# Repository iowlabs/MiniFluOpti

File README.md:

# MiniFluOpti

Versión mini del proyecto FluOpti. Desarrollo conjunto con equipo docente del Instituto de Ingeniería Biológica UC. 
Este proyecto consiste en un controlador de LEDs configurable por I2C. La placa controla 4 canales controladores de LEDs, por medio de señales PWM generadas *on-board*. Los grupos de LEDs considerado para esta versión son: rojos, verde, azul y blanco. Adicionalmente la placa 
incluye un controlador de *heater* y un par de canales de lectura de sensores de temperatura del tipo termistor.

## Características:

* Voltaje de entrada 12[V].
* 4 Canales de salida LEDs: Rojo, Verde, Azul, Blanco.
* 1 Controlador de heater. Max: 12[V] - 3[A]
* 2 Canales de lector de termistor.
* Voltaje de salida para alimentar Rpi 5[V] 2.5[A] (Raspy 3b+)
* Voltaje en placa 3.3[V] para componentes digitales.
* Voltajes disponibles: 3.3[V] 5[V], 9[V] y 12[V]
* Protocolo de control: I2C (deseado)
 
Dependencias:
* Generador de PWMs PCA9685
* Drivers de corriente IRF740
* Drivers de baja corriente (500mA) ULN2803A
* Lector de termistor MAX6682
* Reguladores de voltaje
* Conversores DC-DC

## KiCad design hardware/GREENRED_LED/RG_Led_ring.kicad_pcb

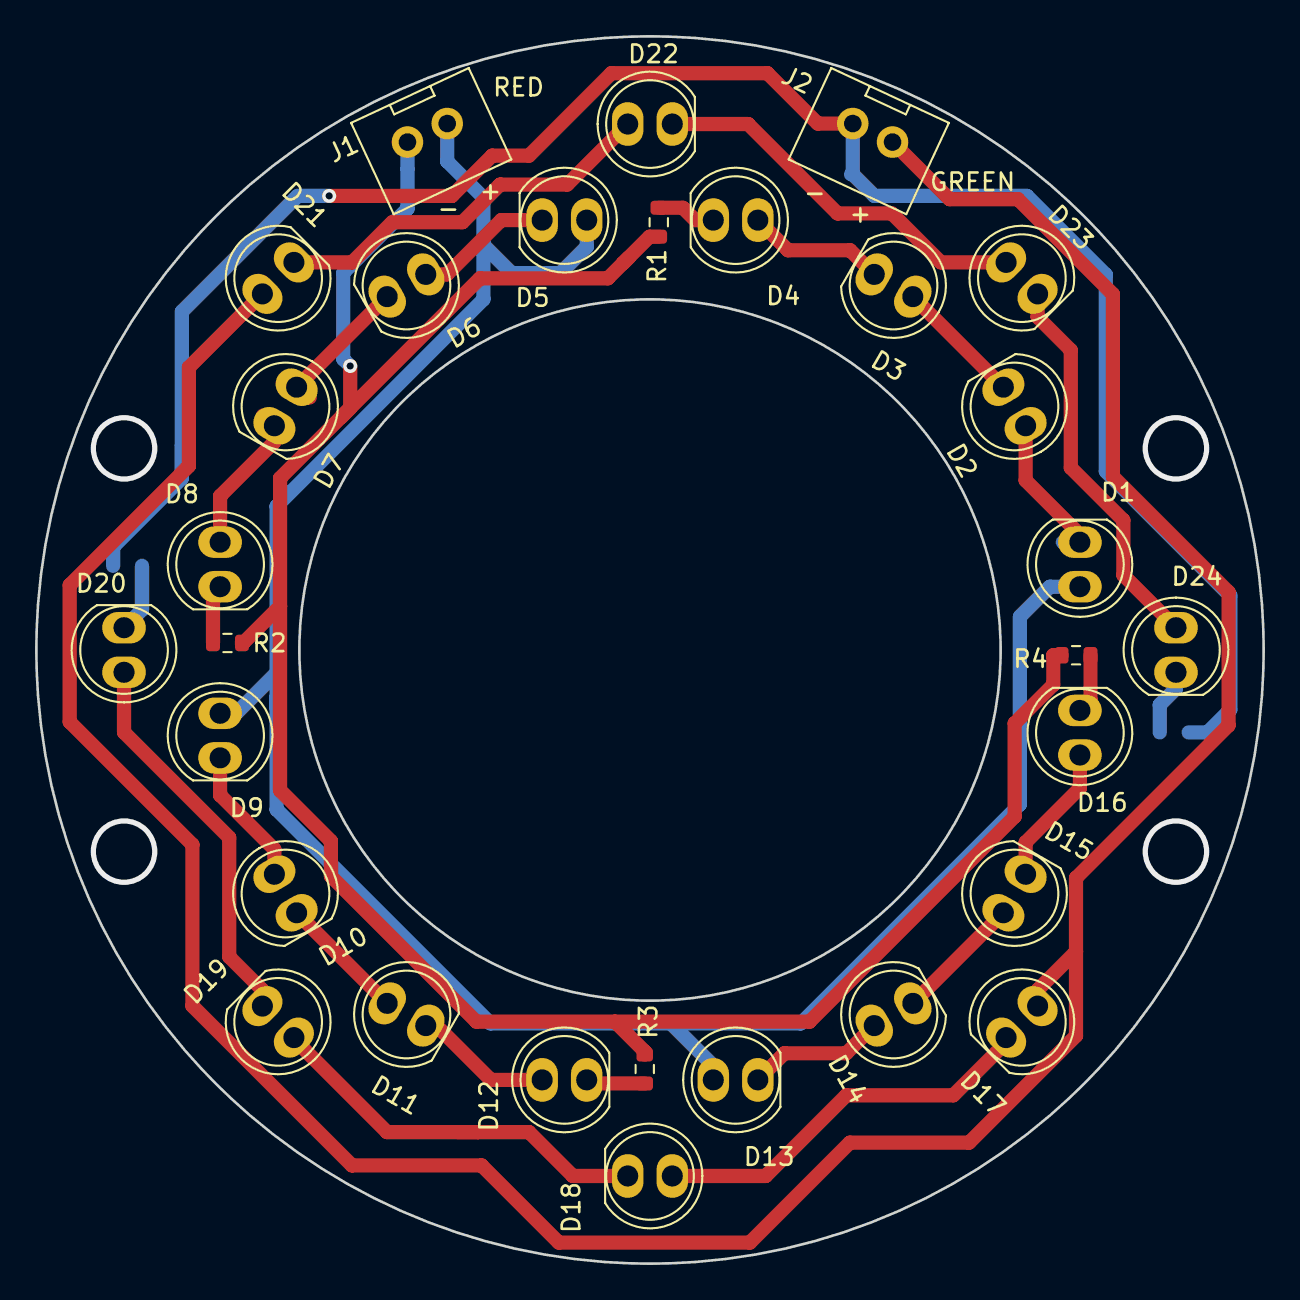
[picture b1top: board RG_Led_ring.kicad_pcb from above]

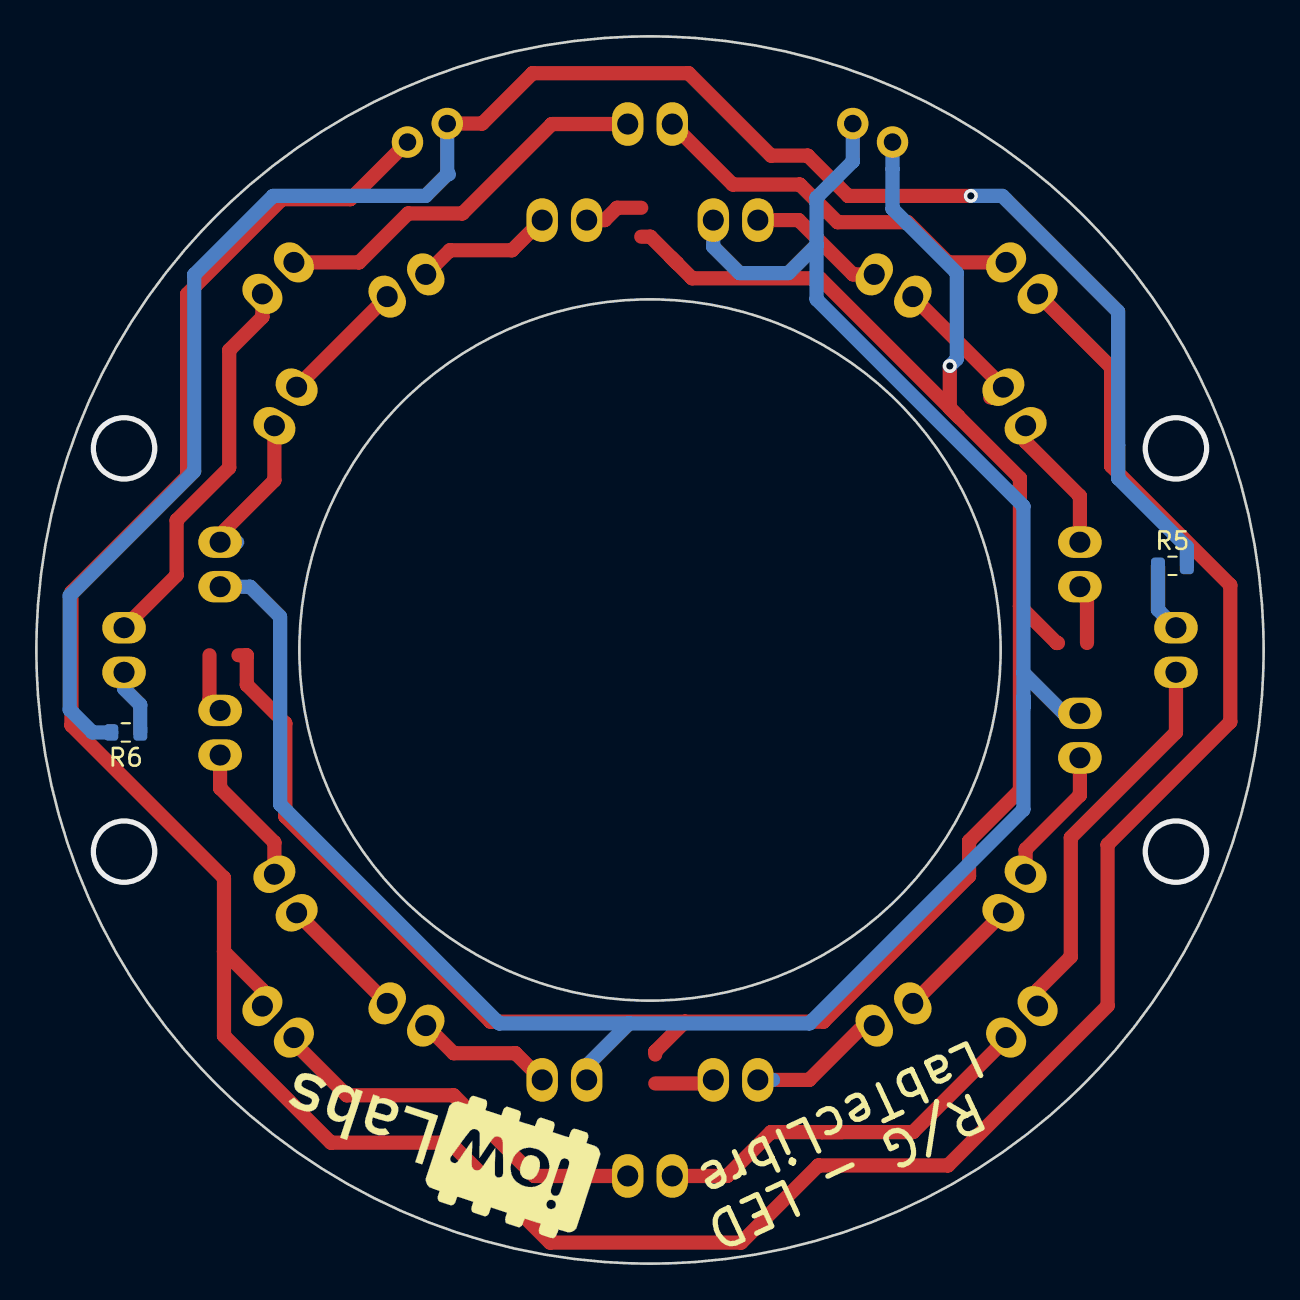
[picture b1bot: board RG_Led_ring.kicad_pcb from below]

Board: 2 copper layers, 70.0 x 70.0 mm, 32 parts (2 on the bottom side), 28 nets.

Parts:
D1, D2, D3, D4, D5, D6, D7, D8, D9, D10, D11, D12, D13, D14, D15, D16, D17, D18, D19, D20, D21, D22, D23, D24: LED; LED_5mm_TH_long
J1, J2: HDR-2x1; JST-XH-2x1-2.5p-TH-V
R1, R2, R3, R4, R5, R6: R_US; R_0603_1608Metric

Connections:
/LED_G+: D17.2, D21.2, J2.1
/LED_G-: J2.2, R5.2, R6.2
/LED_R+: D1.2, D5.2, D9.2, D13.2, J1.1
/LED_R-: J1.2, R1.2, R2.2, R3.2, R4.2
unnamed: D1.1, D2.2
unnamed: D2.1, D3.2
unnamed: D3.1, D4.2
unnamed: D4.1, R1.1
unnamed: D5.1, D6.2
unnamed: D6.1, D7.2
unnamed: D7.1, D8.2
unnamed: D8.1, R2.1
unnamed: D10.1, D11.2
unnamed: D9.1, D10.2
unnamed: D11.1, D12.2
unnamed: D12.1, R3.1
unnamed: D13.1, D14.2
unnamed: D14.1, D15.2
unnamed: D15.1, D16.2
unnamed: D16.1, R4.1
unnamed: D17.1, D18.2
unnamed: D18.1, D19.2
unnamed: D19.1, D20.2
unnamed: D20.1, R5.1
unnamed: D21.1, D22.2
unnamed: D22.1, D23.2
unnamed: D23.1, D24.2
unnamed: D24.1, R6.1

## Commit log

2021-04-06 FluOpti PCB added
2021-04-07 schematic updated
2021-04-08 pcb design
2021-04-12 changes updated
2021-04-12 adding features for the proyect
2021-04-16 adding readme
2021-04-19 changes on description
2021-08-28 Add MiniFluOpti board and blue led board
2021-09-03 minor changes
2021-09-29 adding pdf
2021-10-01 adding some datasheets
2021-12-01 adding ntc functions
2021-12-01 ntc test
2021-12-01 removing debug prints from pi_ntc
2023-08-31 testing leds
2023-09-09 gui v2
2023-10-10 MiniFluOpti first enclosure prototype
2023-11-13 add measurements to RGLED board and related svg and png files
2023-12-19 update the open scad file to create all the 3D componentes of the camera support and LED ring enclosure
2024-01-25 include the RPIv2 camera option for the flat cam holder. Organize files and include STLs and gCodes
